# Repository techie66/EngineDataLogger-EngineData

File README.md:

# Engine Data Logger - Engine Data
This project has been developed using Automake and Makefile setup from: https://github.com/sudar/Arduino-Makefile

Sleepy Pi 2 needs to have software power jumper enabled if programming from the Pi.
	i2cset -y 1 0x24 0xFD
Turn it off with:
	i2cset -y 1 0x24 0xFF

It's not strictly necessary, but Arduino-Makefile includes a script to reset the Arduino. It would need to be setup to set pin 22 of the RPi's GPIO high for about 1/3 of a second. Alternatively, https://github.com/SpellFoundry/avrdude-rpi provides a patched avrdude that handles this for you. This is the approach I have setup here. The Makefile points to a special avr_tools directory that contains this patched version. None of this is necessary if you are willing to manually hit the reset button whenever you try to upload code.

## Componenents
- [EngineDataLogger(EDL)](https://github.com/techie66/EngineDataLogger)
- [EDL - Dashboard](https://github.com/techie66/EngineDataLogger---Dashboard)
- [EDL - Front Controls](https://github.com/techie66/EngineDataLogger-FrontControls)
- ->[EDL - EngineData](https://github.com/techie66/EngineDataLogger-EngineData)

# License
EngineDataLogger is licensed under the GNU GPLv2. Dependencies are licensed under their respective licenses. See LICENSE for full text of GPLv2.

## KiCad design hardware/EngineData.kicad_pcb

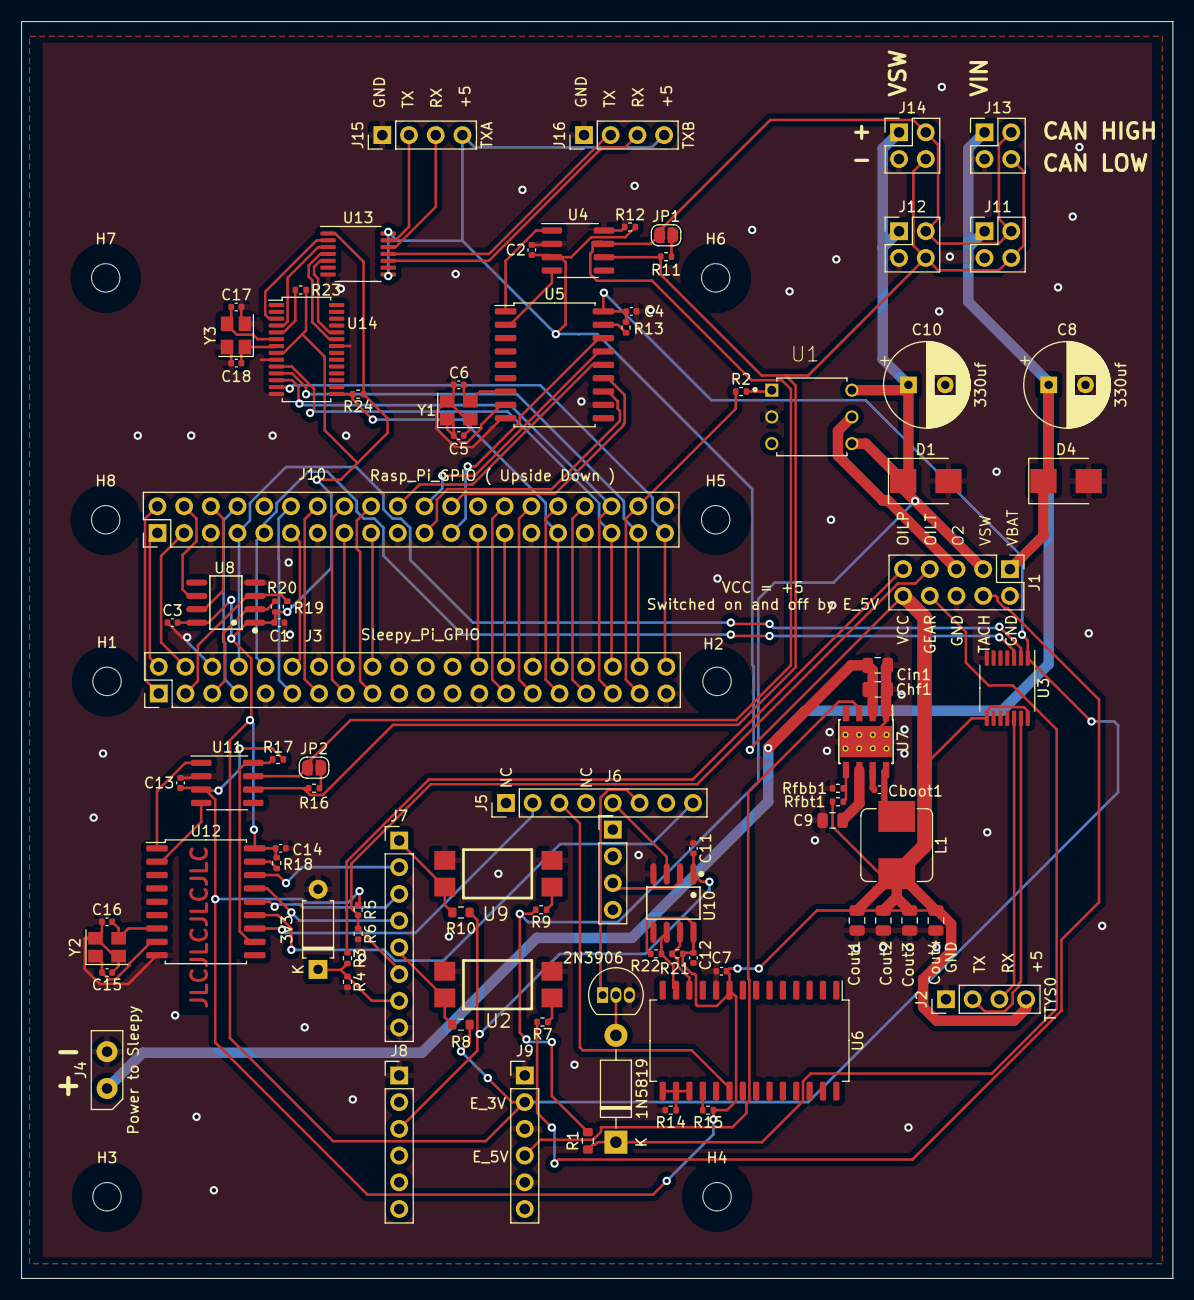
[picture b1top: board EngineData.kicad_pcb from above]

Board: 2 copper layers, 109.5 x 119.5 mm, 100 parts (0 on the bottom side), 98 nets.

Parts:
C1, C2, C3, C4, C7, C11, C12, C13, C14: 100nf; C_0402_1005Metric
C5, C6, C15, C16: 33pf; C_0402_1005Metric
C8, C10: 330uf; CP_Radial_D8.0mm_P3.50mm
C9: 1 uF; C_0805_2012Metric
C17, C18: 30pf; C_0402_1005Metric
Cboot1: 100nf; C_0402_1005Metric
Chf1: 220nf; C_0805_2012Metric
Cin1: 10uf; C_0805_2012Metric
Cout1, Cout2, Cout3, Cout4: 22uF; C_0805_2012Metric
D1, D4: 15V standoff; D_SMB
D2: 1N5819; D_DO-41_SOD81_P10.16mm_Horizontal
D3: 3V3; D_A-405_P7.62mm_Horizontal
H1, H2, H3, H4, H5, H6, H7, H8: MountingHole; MountingHole_2.7mm_M2.5
J1: External Connector; PinHeader_2x05_P2.54mm_Vertical
J2: TTYS0; PinHeader_1x04_P2.54mm_Vertical
J3: Sleepy_Pi_GPIO; PinHeader_2x20_P2.54mm_Vertical
J4: Power to Sleepy; S_Pi_PWR
J5, J7: Conn_01x08; PinHeader_1x08_P2.54mm_Vertical
J6: Conn_01x04; PinHeader_1x04_P2.54mm_Vertical
J8, J9: Conn_01x06; PinHeader_1x06_P2.54mm_Vertical
J10: Rasp_Pi_GPIO ( Upside Down ); PinHeader_2x20_P2.54mm_Vertical
J11, J12, J13, J14: 2x2; PinHeader_2x02_P2.54mm_Vertical
J15: TXA; PinHeader_1x04_P2.54mm_Vertical
J16: TXB; PinHeader_1x04_P2.54mm_Vertical
JP1, JP2: Jumper_NO_Small; SolderJumper-2_P1.3mm_Open_RoundedPad1.0x1.5mm
L1: 8uH, 14m; L_Bourns_SRP7028A_7.3x6.6mm
Q1: 2N3906; TO-92_Inline
R1: 2.2k; R_0603_1608Metric
R2, R3, R4, R19, R20: 2k; R_0402_1005Metric
R5: 470; R_0402_1005Metric
R6, R7, R9, R23, R24: 1k; R_0402_1005Metric
R8, R10: 10k; R_0603_1608Metric
R11, R16: 120R; R_0402_1005Metric
R12, R13, R15, R17, R18: 100k; R_0402_1005Metric
R14, R21, R22: 4K7 1%; R_0402_1005Metric
Rfbb1: 24K9 1%; R_0402_1005Metric
Rfbt1: 100k 1%; R_0402_1005Metric
U1: G3VM-31BR; DIP762W50P254L737H485Q6
U2, U9: EL817; EasyEDA-C183799-smd-SOP-4_L6.5-W4.6-P2.54-LS10.2-TL
U3, U13: TXB0104PW; TSSOP-14_4.4x5mm_P0.65mm
U4, U11: TJA1051T; SOIC-8_3.9x4.9mm_P1.27mm
U5, U12: MCP2515-xSO; SOIC-18W_7.5x11.6mm_P1.27mm
U6: MCP23017-E/SO; SOIC-28W_7.5x18.7mm_P1.27mm
U7: LMR33630ADDA; Texas_HSOP-8-1EP_3.9x4.9mm_P1.27mm_ThermalVias
U8, U10: TCA9517DR; SOIC-8_L4.9-W3.9-P1.27-LS6.0-BL
U14: SC16IS752IPW; TSSOP-28_4.4x9.7mm_P0.65mm
Y1, Y2: 12Mhz; Crystal_SMD_3225-4Pin_3.2x2.5mm
Y3: 14.7456 Mhz; Crystal_SMD_3225-4Pin_3.2x2.5mm

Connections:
3V3: C11.2, J8.3, R10.2, U10.1 (VCCA)
/CAN_H: J11.2, J12.2, J13.2, J14.2, JP1.1 (A), JP2.1 (A), U4.7 (CANH), U11.7 (CANH)
/CAN_L: J11.4, J12.4, J13.4, J14.4, R11.1, R16.1, U4.6 (CANL), U11.6 (CANL)
/GE1: J3.2, J10.1
/GE2: J3.4, J10.3
/GE4: J3.8, J10.7, U3.2 (A1)
/GE5: J3.10, J10.9, U3.3 (A2)
/GE6: J3.12, J10.11
/GE8: J3.16, J10.15
/GE9: J3.18, J10.17
/GE11: J10.21, U5.12 (~INT)
/GE12: J10.23, U5.16 (~CS)
/GE13: J3.26, J10.25
/GE14: J3.28, J10.27
/GE16: J3.32, J10.31, R24.2, U14.15 (~IRQ)
/GE18: J3.36, J10.35, U14.10 (A0/~CS)
/GE19: J3.38, J10.37, U14.11 (A1/SI)
/GE20: J3.40, J10.39, U14.13 (SCL/SCLK)
/GEAR: D2.1 (K), J1.8, R1.1
/GO1: J3.1, J10.2
/GO4: J3.7, J10.8
/GO6: J3.11, J10.12
/GO7: J3.13, J10.14
/GO8: J3.15, J10.16
/GO9: J3.17, J10.18
/GO10: J10.20, U5.14 (SI)
/GO11: J10.22, U5.15 (SO)
/GO12: J10.24, U5.13 (SCK)
/GO14: J3.27, J10.28
/GO15: J3.29, J10.30
/GO16: J3.31, J10.32
/GO17: J3.33, J10.34
/GO18: J3.35, J10.36, U14.12 (n.c./SO)
/GO19: J3.37, J10.38, R2.1
/IO Expander/SCL: R21.1, U6.12 (SCK), U10.7 (SCLB)
/IO Expander/SDA: R22.1, U6.13 (SDA), U10.6 (SDAB)
/MCP2515 w|trans1/EN_TX: R17.1, U11.8 (S), U12.11 (~RX0BF)
/MCP2515 w|trans1/RXCAN: U11.4 (RXD), U12.2 (RXCAN)
/MCP2515 w|trans1/TXCAN: U11.1 (TXD), U12.1 (TXCAN)
/MCP2515 w|trans/RXCAN: U4.4 (RXD), U5.2 (RXCAN)
/MCP2515 w|trans/TXCAN: U4.1 (TXD), U5.1 (TXCAN)
/O2POW: J1.5, U1.5
/OIL_P: J1.9, R3.1
/OIL_T: J1.7, J7.6, R5.2, R6.1
/PB0_8: J5.3, U6.20 (INTA)
/PB1_9: J7.1, R10.1, U9.4
/PB2_10: J7.2, U12.16 (~CS)
/PC1_A1: D3.1 (K), J7.7, R3.2, R4.1
/PD2_2: J7.5, R8.1, U2.4
/PD3_3: J5.6, Q1.1 (E)
/PD6_6: J5.2, U12.12 (~INT)
/PI_SCL: J10.6, U8.7 (SCLB)
/Pi_SDA: J10.4, U8.6 (SDAB)
/SH_SCL: J3.5, R20.2, U8.2 (SCLA)
/SH_SDA: J3.3, R19.2, U8.3 (SDAA)
/S_MISO_12: J7.4, U12.15 (SO)
/S_MOSI_11: J7.3, U12.14 (SI)
/S_SCK: J5.8, U12.13 (SCK)
/S_SCL: J6.3, U10.2 (SCLA)
/S_SDA: J5.5, U10.3 (SDAA)
/TACH: J1.4, R7.2
/UARTs/RST: R23.2, U14.5 (~RESET)
/UARTs/RXA: U13.3 (A2), U14.4 (RXA)
/UARTs/RXB: U13.5 (A4), U14.24 (RXB)
/UARTs/TXA: U13.2 (A1), U14.3 (TXA)
/UARTs/TXB: U13.4 (A3), U14.23 (TXB)
/VBAT: C8.1, Chf1.2, Cin1.2, D4.1 (A1), J1.1, J4.1, J11.1, J13.1, U7.2 (VIN)
/VSW: C10.1, D1.1 (A1), J1.3, J12.1, J14.1, R1.2, R9.2, U1.4, U1.6
E_3V3: C1.2, C3.2, C4.2, C14.2, J9.2, R8.2, R13.2, R18.2, R19.1, R20.1, R23.1, R24.1, U3.1 (VCCA), U5.18 (VDD), U8.1 (VCCA), U8.8 (VCCB), U12.18 (VDD), U13.1 (VCCA), U14.8 (VDD)
E_5V: J9.4, U7.3 (EN)
GND: C1.1, C2.2, C3.1, C4.1, C5.1, C6.1, C7.2, C8.2, C9.1, C10.2, C11.1, C12.1, C13.2, C14.1, C15.1, C16.1, C17.2, C18.1, Chf1.1, Cin1.1, Cout1.2, Cout2.2, Cout3.2, Cout4.2, D1.2 (A2), D3.2 (A), D4.2 (A2), J1.2, J1.6, J2.1, J3.6, J3.9, J3.14, J3.20, J3.25, J3.30, J3.34, J3.39, J4.2, J7.8, J8.1, J9.1, J9.3, J9.5, J10.5, J10.10, J10.13, J10.19, J10.26, J10.29, J10.33, J10.40, J11.3, J12.3, J13.3, J14.3, J15.1, J16.1, Q1.3 (C), R4.2, R6.2, R12.1, R14.2, Rfbb1.2, U1.2, U2.2, U2.3, U3.7 (GND), U4.2 (GND), U4.8 (S), U5.9 (VSS), U5.11 (~RX0BF), U6.10 (VSS), U7.1 (PGND), U7.9 (AGND), U8.4 (GND), U9.2, U9.3, U10.4 (GND), U11.2 (GND), U12.9 (VSS), U13.7 (GND), U14.9 (I2C/~SPI), U14.14 (SDA/VSS), U14.22 (VSS), Y1.2, Y1.4, Y2.2, Y2.4, Y3.2, Y3.4
unnamed: C5.2, U5.8 (OSC1), Y1.1
unnamed: C6.2, U5.7 (OSC2), Y1.3
unnamed: C9.2, U7.6 (VCC)
unnamed: C15.2, U12.8 (OSC1), Y2.1
unnamed: C16.2, U12.7 (OSC2), Y2.3
unnamed: C17.1, U14.6 (XTAL1), Y3.3
unnamed: C18.2, U14.7 (XTAL2), Y3.1
unnamed: Cboot1.1, U7.7 (BOOT)
unnamed: Cboot1.2, L1.1, U7.8 (SW)
unnamed: D2.2 (A), Q1.2 (B)
unnamed: J2.2, U3.13 (B1)
unnamed: J2.3, U3.12 (B2)
unnamed: J15.2, U13.13 (B1)
unnamed: J15.3, U13.12 (B2)
unnamed: J16.2, U13.11 (B3)
unnamed: J16.3, U13.10 (B4)
unnamed: JP1.2 (B), R11.2
unnamed: JP2.2 (B), R16.2
unnamed: R2.2, U1.1
unnamed: R7.1, U2.1
unnamed: R9.1, U9.1
unnamed: R13.1, U5.17 (~RESET)
unnamed: R14.1, U6.15 (A0), U6.16 (A1), U6.17 (A2)
unnamed: R15.2, U6.18 (~RESET)
unnamed: R18.1, U12.17 (~RESET)
unnamed: Rfbb1.1, Rfbt1.1, U7.5 (FB)
VCC: C2.1, C7.1, C12.2, C13.1, Cout1.1, Cout2.1, Cout3.1, Cout4.1, J1.10, J2.4, J15.4, J16.4, L1.2, R5.1, R12.2, R15.1, R17.2, R21.2, R22.2, Rfbt1.2, U3.8 (OE), U3.14 (VCCB), U4.3 (VCC), U6.9 (VDD), U10.8 (VCCB), U11.3 (VCC), U13.8 (OE), U13.14 (VCCB)

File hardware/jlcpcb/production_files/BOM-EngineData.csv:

Comment,Designator,Footprint,LCSC
15V standoff,"D1,D4",D_SMB,C113989
1k,"R23,R24,R6,R7,R9",R_0402_1005Metric,C11702
100nf,"C1,C13,C14,C2,C3,C4,Cboot1",C_0402_1005Metric,C1525
MCP2515-xSO,"U12,U5",SOIC-18W_7.5x11.6mm_P1.27mm,C153782
33pf,"C15,C16,C5,C6",C_0402_1005Metric,C1562
TCA9517DR,U8,SOIC-8_L4.9-W3.9-P1.27-LS6.0-BL,C182421
EL817,"U2,U9",EasyEDA-C183799-smd-SOP-4_L6.5-W4.6-P2.54-LS10.2-TL,C183799
120R,"R11,R16",R_0402_1005Metric,C25079
470,R5,R_0402_1005Metric,C25117
100k,"R12,R13,R17,R18,Rfbt1",R_0402_1005Metric,C25741
10k,"R10,R8",R_0603_1608Metric,C25804
24K9 1%,Rfbb1,R_0402_1005Metric,C25874
1 uF,C9,C_0805_2012Metric,C28323
"8uH, 14m",L1,L_Bourns_SRP7028A_7.3x6.6mm,C408450
2k,"R19,R2,R20,R3,R4",R_0402_1005Metric,C4109
2.2k,R1,R_0603_1608Metric,C4190
10uf,Cin1,C_0805_2012Metric,C440198
22uF,"Cout1,Cout2,Cout3,Cout4",C_0805_2012Metric,C45783
30pf,"C17,C18",C_0402_1005Metric,C5182450
220nf,Chf1,C_0805_2012Metric,C5378
14.7456 Mhz,Y3,Crystal_SMD_3225-4Pin_3.2x2.5mm,C557186
SC16IS752IPW,U14,TSSOP-28_4.4x9.7mm_P0.65mm,C57156
TXB0104PW,"U13,U3",TSSOP-14_4.4x5mm_P0.65mm,C60708
TJA1051T,"U11,U4",SOIC-8_3.9x4.9mm_P1.27mm,C6952
LMR33630ADDA,U7,Texas_HSOP-8-1EP_3.9x4.9mm_P1.27mm_ThermalVias,C841384
12Mhz,"Y1,Y2",Crystal_SMD_3225-4Pin_3.2x2.5mm,C9002
Jumper_NO_Small,JP1,SolderJumper-2_P1.3mm_Open_RoundedPad1.0x1.5mm,
Jumper_NO_Small,JP2,SolderJumper-2_P1.3mm_Open_RoundedPad1.0x1.5mm,

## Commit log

2019-03-16 Initial commit. Basic funtionality.
2019-03-18 separated variables for speed and rpm ISRs
2019-03-18 Changed rotation ISRs to rolling average
2019-03-27 Added initial code to monitor oil temperature, should get moved to its own file.
2019-04-21 Updated constants for Thermistor
2019-04-22 Create LICENSE
2019-04-23 Odometer value read from EEPROM and incremented based off wheel diameter, also stored in EEPROM
2019-04-26 Minor changes
2019-05-03 Put EEPROM structure definition in header. Sending trip data on request.
2019-05-04 Added ability to reset trip via I2C command
2020-03-29 Added support for oil pressure
2023-06-30 New hardware adjustments
    Changed pin numbers. Moved vsw to pin 9, and clarified A0 and A1 instead of 14,15
    Added save odometer every mile.
    Modified conversion for pressure.
2024-02-24 Add hardware files
2024-04-12 Add CAN capabilities
2024-04-13 edit pressure calc
2024-04-13 Makefile adjustments
2024-04-13 fixup CAN messages
2024-04-13 Changed Makefile to run from separate PC as the Pi's serial port is broken
2025-04-24 Changed oil pressure to absolute. Maybe
2025-04-25 Fix, regression oil temp variable size
2025-05-15 Rudimentary compensation of oil pressure with temp.
